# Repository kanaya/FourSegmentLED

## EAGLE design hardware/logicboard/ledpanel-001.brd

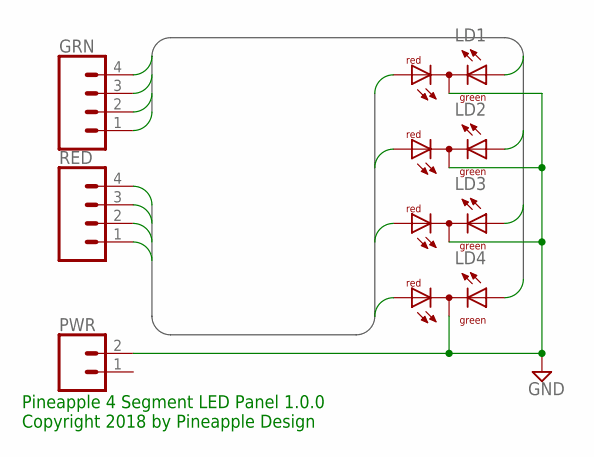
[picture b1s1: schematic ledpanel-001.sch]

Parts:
GRN: CONN_04JST-PTH-VERT; JST-4-PTH-VERT
LD1, LD2, LD3, LD4: DUOLED-RG-C; DUOLED-C-5MM
PWR: CONN_02-JST-2-PTH-NO_SILK; JST-2-PTH-NS
RED: CONN_04JST-PTH-VERT; JST-4-PTH-VERT

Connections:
GND: LD1.C, LD2.C, LD3.C, LD4.C, PWR.2
GREEN1: GRN.1, LD4.AX (AG)
GREEN2: GRN.2, LD3.AX (AG)
GREEN3: GRN.3, LD2.AX (AG)
GREEN4: GRN.4, LD1.AX (AG)
RED1: LD4.AR, RED.1
RED2: LD3.AR, RED.2
RED3: LD2.AR, RED.3
RED4: LD1.AR, RED.4

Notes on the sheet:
Pineapple 4 Segment LED Panel 1.0.0 Copyright 2018 by Pineapple Design

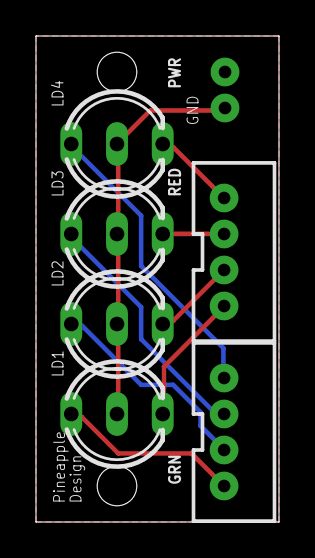
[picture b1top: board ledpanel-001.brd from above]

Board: 2 copper layers, 13.5 x 27.0 mm, 7 parts (0 on the bottom side), 9 nets.

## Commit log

2018-03-05 Initial commit.
2018-03-10 Added PCB data.
2018-03-10 GND.
2018-03-10 Changed dimension.
2018-03-10 Added sample panel.
2018-03-10 Added Makefile.
2018-03-10 Added files.txt.
2018-03-12 Cleared clearance.
2018-03-15 Modified silk pattern.
2018-03-16 Added Silk pattern.
2018-03-16 Fixed error.

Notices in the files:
parts and their libraries:
SparkFun-Connectors: Licensing: Creative Commons ShareAlike 4.0 International - https://creativecommons.org/licenses/by-sa/4.0
